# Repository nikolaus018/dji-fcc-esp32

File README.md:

<h1 align="center">dji-fcc-esp32</h1>

<p align="center">
  <b>A pocket dongle that switches a DJI N1 remote to FCC mode, instead of a phone and an app.</b><br>
  Plug it in, it patches over USB, shows the result on an LED and goes back to sleep.
</p>

<p align="center">

</p>

## What is in here

- **Firmware** (ESP-IDF): USB host stack for the remote's CDC-ACM interface, with Espressif's USB component patched to cope with the remote's
  512-byte bulk packets on a full-speed link.
- **Hardware** ([`hardware/`](hardware/README.md)): a complete KiCad design for a battery-powered dongle, generated from one Python source of truth:
  schematic, autorouted 2-layer PCB, gerbers, JLCPCB BOM and placement, STEP model. 0 DRC errors.
- **Web flasher** ([live](https://nikolaus018.github.io/dji-fcc-esp32/), source in [`webflasher/`](webflasher/)): flash either build from Chrome or Edge over Web Serial. Built and deployed by CI on every push.

The two packets come from [DJI-FCC-HACK](https://github.com/M4TH1EU/DJI-FCC-HACK) (credit to galbb on MavicPilots);
this project replaces its Android app.

## Two ways to run it

* **Dev board** (any ESP32-S3 with a native USB port): default build, instructions below.
* **Custom PCB** (battery powered dongle, charge over USB-C, sleeps between uses): see [`hardware/`](hardware/README.md).
  Build the firmware for it with
  ```bash
  idf.py -B build_custom -DSDKCONFIG=sdkconfig.custom -DSDKCONFIG_DEFAULTS=sdkconfig.board_custom -DIDF_TARGET=esp32s3 build
  ```

## Use (dev board)
1. Flash through the **COM** port: `idf.py -p <port> flash`
2. Close the **USB-OTG** solder pad on the board bottom so it can power the remote's port.
3. Power on the drone and remote, wait until connected. The phone must **not** be connected to the remote while patching.
4. Plug the board's **USB** port into the remote's **bottom** port.
5. LED: blue = waiting, yellow = sending, green = sent, red = error.
6. Unplug the board and connect your phone to the **top** port.

The patch must be repeated **every time** you power on the drone and remote.

FCC power is only legal in the US; power cycle the drone and remote to return to CE.

## Flashing the custom PCB
Plug **J2** into your computer and run `idf.py -B build_custom ... -p <port> flash` (port is the ESP's built-in USB-Serial-JTAG). Details in
[`hardware/README.md`](hardware/README.md#flashing-and-updates).

## Notes
- The remote reports 512-byte bulk packets on a full-speed link. `components/espressif__usb` is a copy of
  Espressif's USB host component with the MPS check in `hcd_dwc.c` relaxed, and `main/dji.c` sizes the
  non-periodic TX FIFO for it. Both are required.
- The CDC serial function is interface 2; interfaces 0/1 are DJI-proprietary.
- The LED code drives GPIO48 and GPIO38 (DevKitC-1 v1.0 / v1.1).
- `main/board.h` is the board abstraction (`board_devkit.c` / `board_custom.c`); `main/dji.c` holds the patch logic.
- The dev-board build was tested on a real remote; the custom-PCB firmware compiles but, like the hardware itself, has never run on a real board (see `hardware/README.md`).

## License
MIT for this project's own code (see `LICENSE`). `components/espressif__usb` is Apache-2.0 (Espressif), see its own `LICENSE`.

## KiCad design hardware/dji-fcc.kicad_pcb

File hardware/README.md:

# dji-fcc-esp32 hardware (rev A)

A small battery-powered dongle that replaces the Android phone in the DJI N1 "FCC patch" workflow:
plug it into the remote's **bottom** USB-C port, it powers the port, sends the patch, shows the result on an LED
and goes back to sleep. Charge it over USB-C.

**Status: rev A, ready to order a prototype batch. Not yet built or tested on real hardware.**
Everything below was checked by KiCad ERC/DRC and by cross-checking datasheets; nothing has been powered up.
See [Before you call it production](#before-you-call-it-production).

## What it does

```
 J2 USB-C (charge + flash)     J1 USB-C (to the remote's bottom port)
   │ 5 V, D+/D-                   ▲ 5 V, ~540 mA limit      D+/D-/CC
   ▼                              │                          │
 TP4056 charger ──► VBAT ──► MT3608 boost ──► TPS2553 switch ─┤
 (255 mA)            │  ▲        (5.0 V)        (EN from ESP)  │
                     │  └── DW01A + FS8205A protection        │
                     ▼                                        ▼
                  AP2112K 3.3 V ──► ESP32-S3-MINI-1-N8 ◄─ FSUSB42 ◄─ USBLC6 ESD (J1)
                                      │ ADC: CC1/CC2 (attach), VBAT   ▲   (select = J2 has VBUS)
                                      └ RGB status LED, UART pads     └─ USBLC6 ESD (J2)
```

Behaviour (firmware `main/`, built with `CONFIG_DJI_BOARD_CUSTOM`):

1. Deep sleep (~85 µA). The two CC pins of J1 idle high (33 kΩ pull-ups to 3V3).
2. The remote's 5.1 kΩ Rd pulls a CC pin low on plug-in → ESP wakes (EXT1).
3. Battery check (< 3.3 V → red blinks, sleep). Blue LED. Boost on, switch on → remote gets VBUS and enumerates.
4. Patch is sent over the remote's CDC-ACM interface. Yellow while sending, **green = success, red = failure**.
5. Port power off, deep sleep. Each plug-in is patched once: leaving the dongle in the remote does not keep it
   awake or drain the battery; unplug and plug it in again after every power-on of the drone/remote.

LED colours: blue = powering remote, yellow = sending, green = patched, red = error / low battery.
While J2 is powered the same RGB LED shows charging (red) / full (green) / powered but not charging (blue).

## Files

| Path | What |
|---|---|
| `design.py` | Single source of truth: every part, value, footprint and net. |
| `gen_sch.py` → `dji-fcc.kicad_sch` | Generates the schematic (nets as global labels, one sheet). |
| `gen_pcb.py`, `placement.json`, `route.py`, `tools/route.sh` | Placement → Freerouting → import → ground pours, stitching vias → DRC. |
| `dji-fcc.kicad_pcb` / `.kicad_pro` | The board. Open in KiCad 9/10. |
| `lib/dji_parts.kicad_sym` | Custom symbols (FS8205A, TPS2553). |
| `fab/` | `dji-fcc-gerbers.zip`, `bom_jlcpcb.csv`, `cpl_jlcpcb.csv`, `bom_full.csv`, `dji-fcc.step`, raw gerbers/drill. |
| `docs/` | `schematic.pdf`, `pcb_top.pdf`, `pcb_bottom.pdf`, renders. |

Regenerate everything (needs KiCad, `uv`, Java and Freerouting; paths are set in `tools/env.sh` and can be
overridden with `KICAD_APP`, `JAVA`, `FREEROUTING`):

```bash
cd hardware
uv run --with kiutils python gen_sch.py     # schematic + pin map
PASSES=100 tools/route.sh                   # placement, autoroute (retries), pours, DRC
tools/fab.sh                                # gerbers, drill, BOM, CPL, PDFs, STEP
```

Edit parts/nets in `design.py` and positions in `placement.json`; do not hand-edit the generated KiCad files
unless you stop using the generators.

## Board

* 80 × 34 mm, 1.6 mm, 2-layer, all parts on top (single-sided SMT assembly), 2 mm corner radius.
* Net classes: power 0.6 mm (routed down to 0.4–0.45 mm at pads), signals 0.2 mm, ≥ 0.1 mm minimum, vias 0.6/0.3 (0.8/0.4 power).
* Ground pour on both layers with stitching vias; DRC: 0 errors, 0 unconnected. Schematic parity checked.
* Antenna keepout of the ESP module sits at the top edge (the radio is unused, but nothing is placed there).

### Enclosure interface

| Item | Position (mm, origin top-left, +y down) |
|---|---|
| J1 USB-C (to remote) | mouth flush with left edge, centre y = 17, shell 8.94 wide × 3.3 high |
| J2 USB-C (charge + flash) | mouth flush with right edge, centre y = 17 |
| Status LEDs R/G/B | (67, 2.2), (71, 2.2), (75, 2.2): light-pipe window in the top-right corner |
| Mounting holes | 2 × Ø2.2 (M2) at (3, 31) and (77, 31) |
| Battery | JST-PH 2 mm at (36, 27.4); a 502040 pouch (≈ 5 × 20 × 40 mm, 400-500 mAh) fits under the board |
| Programming/test pads | bottom edge x = 42.5 … 53, y = 32.7 (EN, IO0, TX, RX, 3V3); GND/VBAT/VBUS pads top-left |
| Tallest parts | JST connector 5.5 mm, USB-C 3.3 mm, module 2.4 mm, inductor 2.0 mm |

`fab/dji-fcc.step` contains the board and component models for fitting a case. Keep metal away from the top edge
(antenna end of the module). Both USB-C ports are exposed in the default layout. J2 is needed for charging and updates, so a case that hides it needs a cover or
a charge/update door; J1 is the one used every flight.

## Ordering (JLCPCB)

1. Upload `fab/dji-fcc-gerbers.zip`: 2 layers, 1.6 mm, any surface finish (HASL is fine; ENIG nicer for USB-C).
2. Enable SMT assembly, **top side**, upload `fab/bom_jlcpcb.csv` and `fab/cpl_jlcpcb.csv`.
3. In the placement viewer **check rotation of every polarised part** (U1..U7, Q1, J1..J3, D1..D8, L1).
   JLCPCB's part library often needs per-part rotation offsets (`cpl_jlcpcb.csv` uses KiCad's rotation as-is).
4. Hand-fit afterwards: battery (pre-wired JST-PH 2.0 pack, **polarity: + on pin 1, silkscreen shows + and -**).
   Many packs are wired the other way round; check with a meter before connecting.
5. Flash over J2 (below), then run the bring-up list.

`fab/bom_full.csv` lists every line with MPN and LCSC number. Numbers were looked up on jlcpcb.com on 2026-10-11:
every line resolved to a matching part (L1, C48427, is listed as Sunlord SWPA4020S4R7MT, 4.7 µH, rated 1.34 A / 2.5 A). **Stock and "basic vs extended" status change, re-check before ordering.**
Q1 is ordered as HXY MOSFET 8205A (C5148694) because the Fortune FS8205A was out of stock; 8205A parts in TSSOP-8
share one pinout (1/8 drain, 2/3 source 1, 4 gate 1, 5 gate 2, 6/7 source 2), and the HXY datasheet drawing matches it.
The DW01A pin order was checked against the YONGYUTAI datasheet for C2927799 (1 OD, 2 CSI, 3 OC, 4 NC, 5 VDD,
6 VSS; over-charge 4.30 V, over-discharge 2.40 V).

## Flashing and updates

**Over J2 (USB-C), no adapter needed.** The ESP32-S3 has one USB port. A small switch (FSUSB42) connects it to J2 whenever J2 has
5 V on it (a computer or charger plugged in) and to J1 otherwise. Plug J2 into a computer:

1. The board wakes (VBUS on J2 is a wake source), sees the charger and stays out of USB host mode. The RGB LED shows charge state.
2. The ESP's built-in USB-Serial-JTAG shows up as a serial port (VID 303A, PID 1001).
3. `idf.py -B build_custom ... -p <port> flash`. esptool resets into the ROM bootloader by itself (no buttons).

If the firmware is ever broken so badly that step 2 does not work, short the **IO0** pad to GND while plugging J2 in: the ROM
bootloader takes over USB. The UART pads (TX, RX, GND, 3V3, EN, IO0) remain as a last resort and for production jigs.
Do not power the 3V3 pad while the battery is connected.

On a computer the ESP stays awake for as long as the host talks to it, so the port does not disappear mid-flash.
On a plain charger it sleeps and only wakes every 30 s for about 2 s to refresh the LED (which stays lit through
the sleep). That matters: the awake ESP draws more than the TP4056's 25 mA end-of-charge threshold, so a board that
stayed awake would never finish charging. For the same reason the LED may not reach green while J2 is on a computer.

## Design notes

* **Remote port:** Rp = 33 kΩ to 3V3 on both CC pins (spec: 36 kΩ ±20 % = default USB power). VBUS comes from an
  MT3608 boost (FB divider 220 k/30 k → 5.0 V) through a TPS2553 (R_ILIM 47 kΩ ≈ 540 mA, reverse-blocking, /FAULT to the ESP).
  The boost output is not isolated when disabled (battery minus a diode drop leaks to its output), the switch is what keeps the port dead.
* **Charger:** TP4056, R_PROG 4.7 kΩ → 255 mA (≈ 0.5 C for a 500 mAh cell), TEMP tied to GND (no NTC), CE tied high.
* **Protection:** DW01A + FS8205A in the battery negative leg (net `BNEG` ↔ `GND`), so the pack cannot over-discharge even
  if the firmware misbehaves. Still use a good cell; protection ICs are not a substitute.
* **LDO:** AP2112K-3.3 directly from VBAT. Below ≈ 3.55 V the rail sags (dropout), the firmware refuses to start the remote below 3.3 V.
* **Sleep current:** AP2112K 55 µA + S3 deep sleep ~7 µA + DW01A ~3 µA + dividers ~17 µA ≈ 85 µA → months of standby on 500 mAh.
* **Status LEDs** sit between VBAT and the GPIOs (sinking, GPIO low = on) so the blue LED still has headroom at 3.3 V.
* **USB data path:** FSUSB42 (VCC 3.3 V, OE tied low, SEL = J2-VBUS divider output). SEL low → J1 (remote), SEL high → J2 (computer).
  Each connector has its own USBLC6 ESD array.
* **Pins used:** IO1/IO2 CC1/CC2 (ADC1, wake), IO4 VBAT sense (ADC1), IO6 boost EN, IO7 switch EN, IO8 /FAULT, IO21 J2-VBUS sense (wake),
  IO38 /STDBY, IO39 /CHRG (internal pull-ups), IO40/41/42 LED B/G/R, IO19/IO20 USB, TXD0/RXD0 UART pads, IO0/EN pads.

## Before you call it production

This is a prototype-ready design, not a production release. Open items, roughly in order:

1. **Build 5 boards and bring them up.** Checklist:
   - Visual / continuity: no shorts VBAT-GND, 3V3-GND, VBUS_REM-GND with the battery out.
   - Charge port: 5 V in → RGB LED red while charging, green when full, TP4056 BAT ≈ 4.2 V at end of charge, 255 mA max.
   - **USB switch:** with J2 on a computer the ESP enumerates as 303A:1001 and flashes; with only J1 plugged into a remote it enumerates the remote.
     Check both directions, also with both cables attached (J2 wins).
   - Protection: a DW01A usually stays off after the battery is first connected until a charger is applied once;
     plug J2 in before judging a "dead" board. Then, battery connected, measure VBAT at J3 vs. 3V3 pad; short-circuit test on a bench supply with current limit.
   - Boost: VBOOST = 5.0 V ± 3 % with 100 Ω load, ripple < 100 mV; `BOOST_EN` low → switch output < 0.1 V.
   - Switch: VBUS_REM = 0 V when idle, 5 V when enabled, trips at ≈ 0.5-0.6 A.
   - **J1 CC behaviour with a real remote:** confirm CC reads ≈ 0.44 V when plugged and the board wakes. If a remote variant
     does not present Rd, the wake logic needs a fallback (timer wake + VBUS probe). Also check that unplugging wakes
     the board once and that it then sleeps again (the firmware re-arms the wake-up for the opposite CC level).
   - Sleep / charge: sleep current ≈ 85 µA with and without a remote left plugged in; on a wall charger the LED goes
     red → green and the TP4056 terminates.
   - Full patch cycle on every drone/remote you care about (README of DJI-FCC-HACK lists tested ones).
2. **Verify placement rotations** in the JLCPCB viewer and on the first assembled board.
3. **Battery:** a protected 1S LiPo with PH-2.0 lead and the polarity you expect. Mechanical retention and a label on the case.
4. **Compliance** (needed to sell it): FCC Part 15B / CE EMC for an unintentional radiator that contains a pre-certified module,
   UN38.3 transport test for the battery, RoHS paperwork. Also check the legal side of selling a product whose purpose is to switch
   a DJI remote to its FCC power profile.
5. Firmware: measure the brown-out margin with a nearly empty cell (a brown-out reset is reported as low battery and
   not retried until the next plug-in).

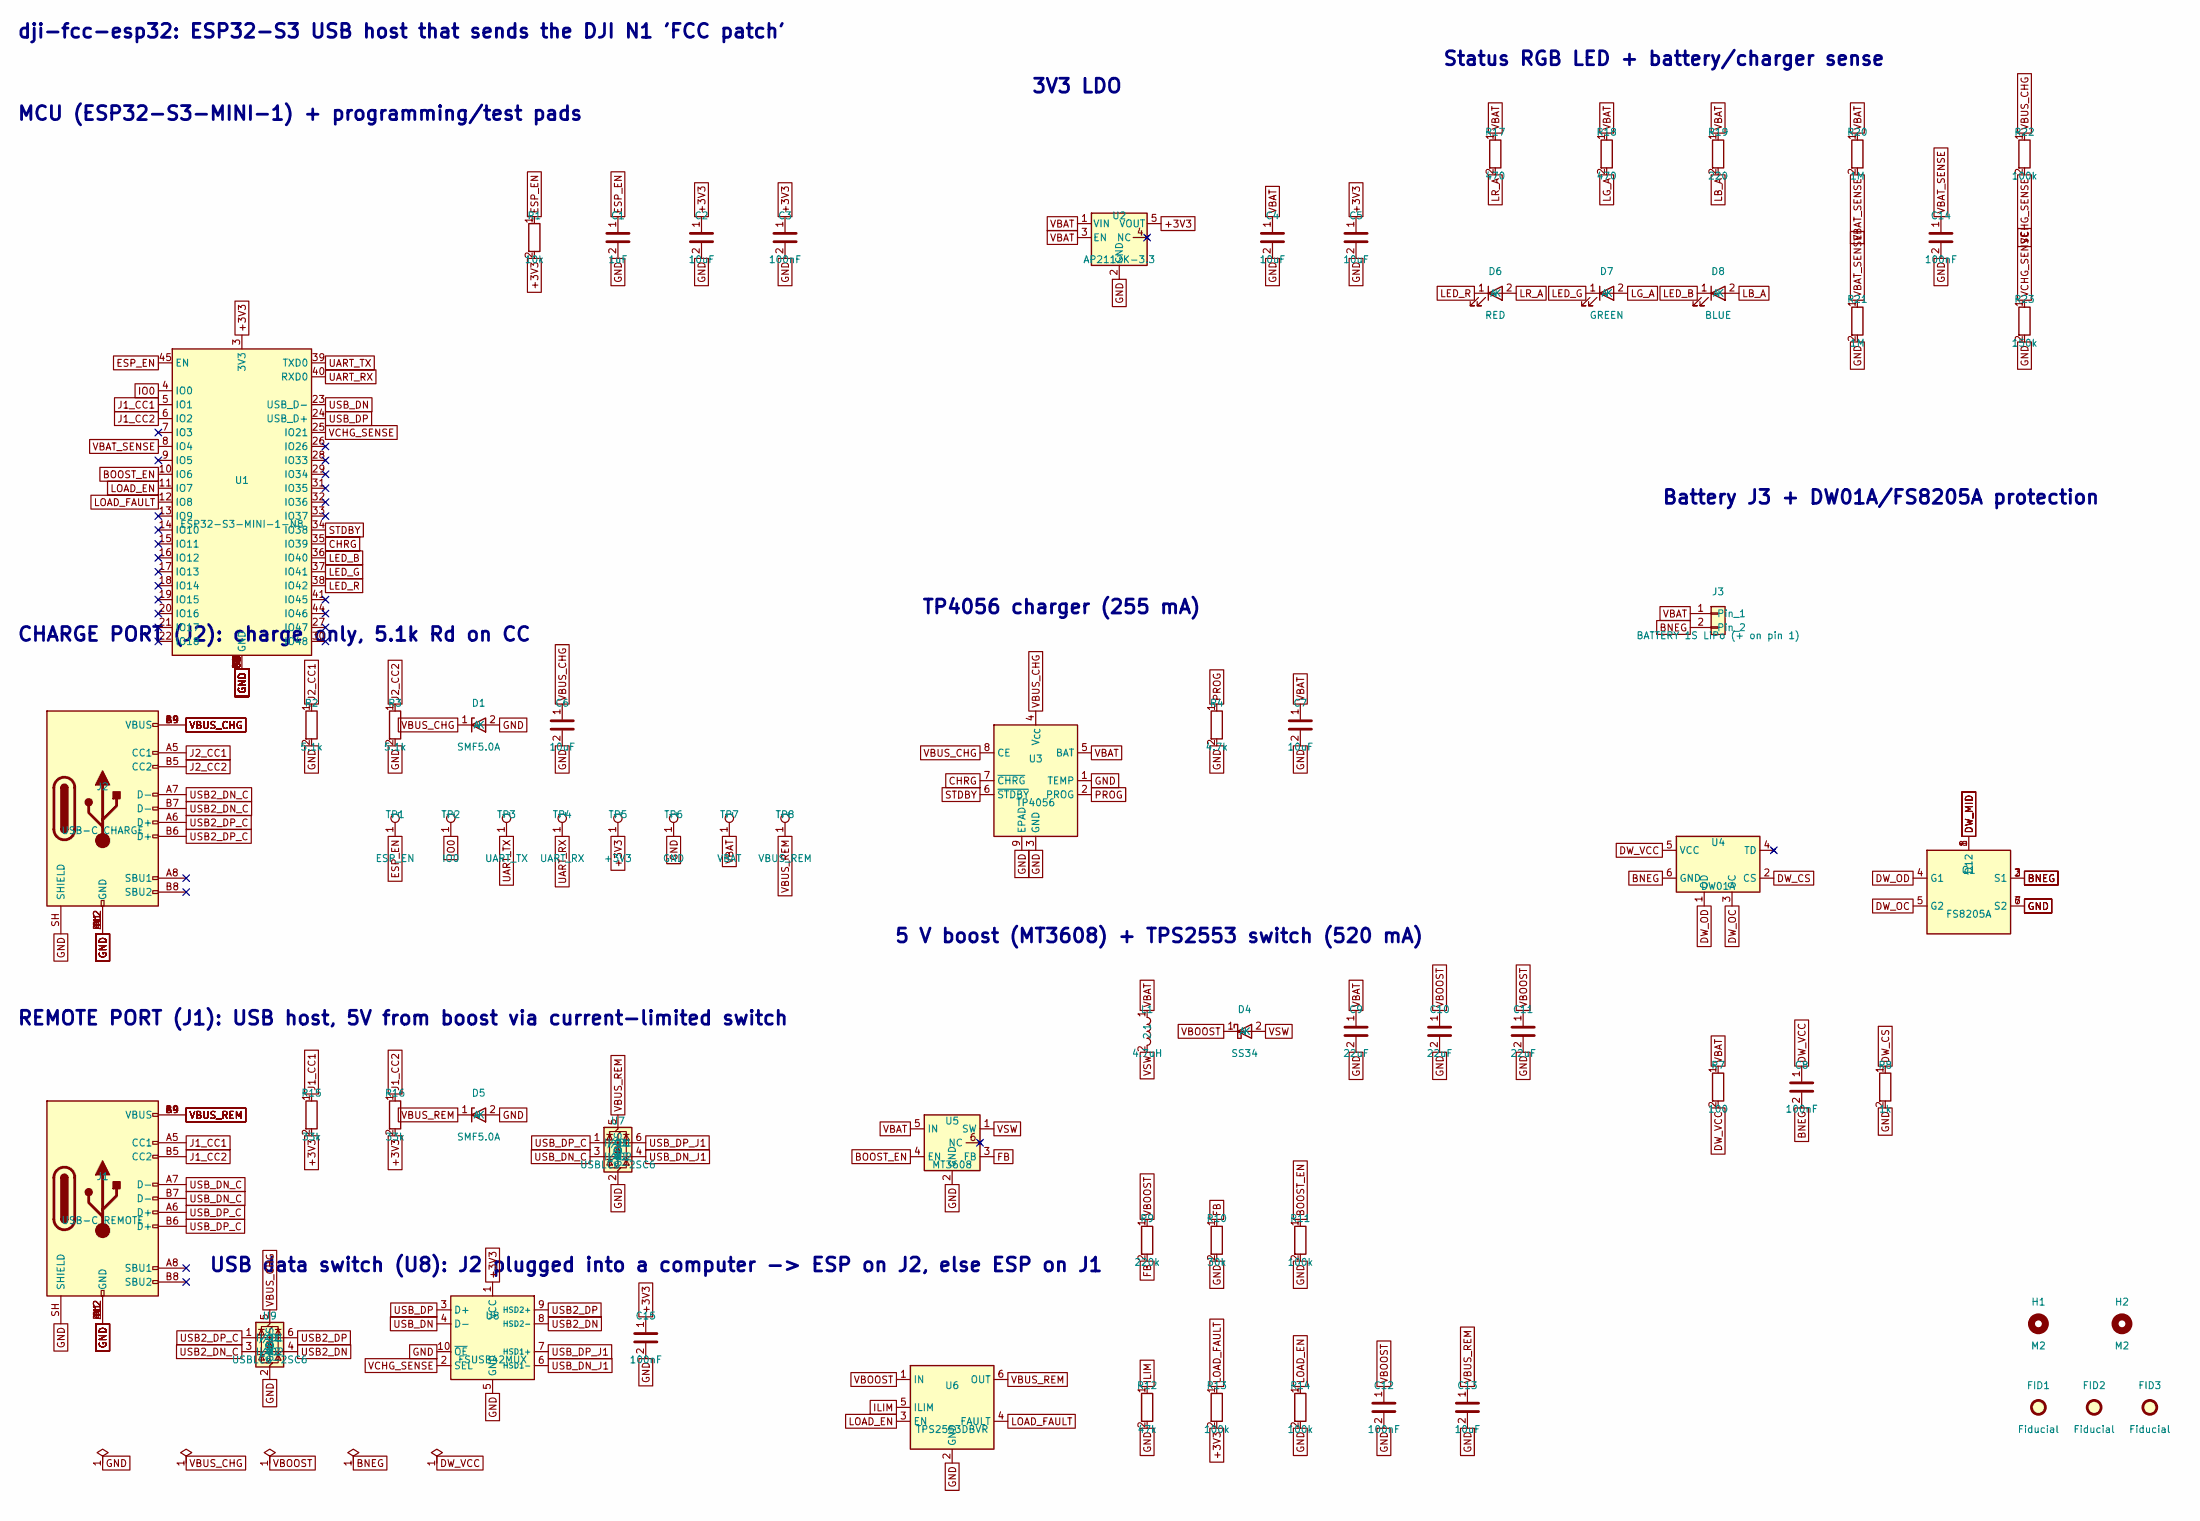
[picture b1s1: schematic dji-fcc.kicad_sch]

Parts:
C1: 1uF; C_0603_1608Metric
C2, C4, C5, C6, C7, C13: 10uF; C_0805_2012Metric
C3, C8, C12, C14, C15: 100nF; C_0603_1608Metric
C9, C10, C11: 22uF; C_0805_2012Metric
D1, D5: SMF5.0A; D_SOD-123F; MPN SMF5.0A
D4: SS34; D_SMA; MPN SS34
D6: RED; LED_0603_1608Metric
D7: GREEN; LED_0603_1608Metric
D8: BLUE; LED_0603_1608Metric
FID1, FID2, FID3: Fiducial; Fiducial_0.5mm_Mask1mm
H1, H2: M2; MountingHole_2.2mm_M2
J1: USB-C REMOTE; USB_C_Receptacle_HRO_TYPE-C-31-M-12; MPN TYPE-C-31-M-12
J2: USB-C CHARGE; USB_C_Receptacle_HRO_TYPE-C-31-M-12; MPN TYPE-C-31-M-12
J3: BATTERY 1S LiPo (+ on pin 1); JST_PH_S2B-PH-SM4-TB_1x02-1MP_P2.00mm_Horizontal; MPN S2B-PH-SM4-TB
L1: 4.7uH; L_Sunlord_SWPA4020S; MPN SWPA4020S4R7MT
Q1: FS8205A; TSSOP-8_4.4x3mm_P0.65mm; MPN FS8205A
R1: 10k; R_0603_1608Metric
R2, R3: 5.1k; R_0603_1608Metric
R4: 4.7k; R_0603_1608Metric
R7: 100; R_0603_1608Metric
R8: 1k; R_0603_1608Metric
R9: 220k; R_0603_1608Metric
R10: 30k; R_0603_1608Metric
R11, R13, R14, R22: 100k; R_0603_1608Metric
R12: 47k; R_0603_1608Metric
R15, R16: 33k; R_0603_1608Metric
R17, R18: 470; R_0603_1608Metric
R19: 220; R_0603_1608Metric
R20, R21: 1M; R_0603_1608Metric
R23: 150k; R_0603_1608Metric
TP1: ESP_EN; TestPoint_Pad_D1.5mm
TP2: IO0; TestPoint_Pad_D1.5mm
TP3: UART_TX; TestPoint_Pad_D1.5mm
TP4: UART_RX; TestPoint_Pad_D1.5mm
TP5: +3V3; TestPoint_Pad_D1.5mm
TP6: GND; TestPoint_Pad_D1.5mm
TP7: VBAT; TestPoint_Pad_D1.5mm
TP8: VBUS_REM; TestPoint_Pad_D1.5mm
U1: ESP32-S3-MINI-1-N8; ESP32-S2-MINI-1; MPN ESP32-S3-MINI-1-N8
U2: AP2112K-3.3; SOT-23-5; MPN AP2112K-3.3TRG1
U3: TP4056; SOIC-8-1EP_3.9x4.9mm_P1.27mm_EP2.41x3.3mm; MPN TP4056-42-ESOP8
U4: DW01A; SOT-23-6; MPN DW01A
U5: MT3608; SOT-23-6; MPN MT3608
U6: TPS2553DBVR; SOT-23-6; MPN TPS2553DBVR
U7, U9: USBLC6-2SC6; SOT-23-6; MPN USBLC6-2SC6
U8: FSUSB42MUX; MSOP-10_3x3mm_P0.5mm; MPN FSUSB42MUX

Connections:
+3V3: C2.1, C3.1, C5.1, C15.1, R1.2, R13.2, R15.2, R16.2, TP5.1, U1.3 (3V3), U2.5 (VOUT), U8.1 (VCC)
BNEG: C8.2, J3.2, Q1.2 (S1), Q1.3 (S1), U4.6 (GND)
BOOST_EN: R11.1, U1.10 (IO6), U5.4 (EN)
CHRG: U1.35 (IO39), U3.7 (~CHRG)
DW_CS: R8.1, U4.2 (CS)
DW_MID: Q1.1 (D12), Q1.8 (D12)
DW_OC: Q1.5 (G2), U4.3 (OC)
DW_OD: Q1.4 (G1), U4.1 (OD)
DW_VCC: C8.1, R7.2, U4.5 (VCC)
ESP_EN: C1.1, R1.1, TP1.1, U1.45 (EN)
FB: R9.2, R10.1, U5.3 (FB)
GND: C1.2, C2.2, C3.2, C4.2, C5.2, C6.2, C7.2, C9.2, C10.2, C11.2, C12.2, C13.2, C14.2, C15.2, D1.2 (A), D5.2 (A), J1.A1 (GND), J1.A12 (GND), J1.B1 (GND), J1.B12 (GND), J1.SH (SHIELD), J2.A1 (GND), J2.A12 (GND), J2.B1 (GND), J2.B12 (GND), J2.SH (SHIELD), Q1.6 (S2), Q1.7 (S2), R2.2, R3.2, R4.2, R8.2, R10.2, R11.2, R12.2, R14.2, R21.2, R23.2, TP6.1, U1.1 (GND), U1.2 (GND), U1.42 (GND), U1.43 (GND), U1.46 (GND), U1.47 (GND), U1.48 (GND), U1.49 (GND), U1.50 (GND), U1.51 (GND), U1.52 (GND), U1.53 (GND), U1.54 (GND), U1.55 (GND), U1.56 (GND), U1.57 (GND), U1.58 (GND), U1.59 (GND), U1.60 (GND), U1.61 (GND), U1.62 (GND), U1.63 (GND), U1.64 (GND), U1.65 (GND), U2.2 (GND), U3.1 (TEMP), U3.3 (GND), U3.9 (EPAD), U5.2 (GND), U6.2 (GND), U7.2 (GND), U8.5 (GND), U8.10 (~OE), U9.2 (GND)
ILIM: R12.1, U6.5 (ILIM)
IO0: TP2.1, U1.4 (IO0)
J1_CC1: J1.A5 (CC1), R15.1, U1.5 (IO1)
J1_CC2: J1.B5 (CC2), R16.1, U1.6 (IO2)
J2_CC1: J2.A5 (CC1), R2.1
J2_CC2: J2.B5 (CC2), R3.1
LB_A: D8.2 (A), R19.2
LED_B: D8.1 (K), U1.36 (IO40)
LED_G: D7.1 (K), U1.37 (IO41)
LED_R: D6.1 (K), U1.38 (IO42)
LG_A: D7.2 (A), R18.2
LOAD_EN: R14.1, U1.11 (IO7), U6.3 (EN)
LOAD_FAULT: R13.1, U1.12 (IO8), U6.4 (FAULT)
LR_A: D6.2 (A), R17.2
PROG: R4.1, U3.2 (PROG)
STDBY: U1.34 (IO38), U3.6 (~STDBY)
UART_RX: TP4.1, U1.40 (RXD0)
UART_TX: TP3.1, U1.39 (TXD0)
USB2_DN: U8.8 (HSD2-), U9.4 (I/O2)
USB2_DN_C: J2.A7 (D-), J2.B7 (D-), U9.3 (I/O2)
USB2_DP: U8.9 (HSD2+), U9.6 (I/O1)
USB2_DP_C: J2.A6 (D+), J2.B6 (D+), U9.1 (I/O1)
USB_DN: U1.23 (USB_D-), U8.4 (D-)
USB_DN_C: J1.A7 (D-), J1.B7 (D-), U7.3 (I/O2)
USB_DN_J1: U7.4 (I/O2), U8.6 (HSD1-)
USB_DP: U1.24 (USB_D+), U8.3 (D+)
USB_DP_C: J1.A6 (D+), J1.B6 (D+), U7.1 (I/O1)
USB_DP_J1: U7.6 (I/O1), U8.7 (HSD1+)
VBAT: C4.1, C7.1, C9.1, J3.1, L1.1, R7.1, R17.1, R18.1, R19.1, R20.1, TP7.1, U2.1 (VIN), U2.3 (EN), U3.5 (BAT), U5.5 (IN)
VBAT_SENSE: C14.1, R20.2, R21.1, U1.8 (IO4)
VBOOST: C10.1, C11.1, C12.1, D4.1 (K), R9.1, U6.1 (IN)
VBUS_CHG: C6.1, D1.1 (K), J2.A4 (VBUS), J2.A9 (VBUS), J2.B4 (VBUS), J2.B9 (VBUS), R22.1, U3.4 (V_{CC}), U3.8 (CE), U9.5 (VBUS)
VBUS_REM: C13.1, D5.1 (K), J1.A4 (VBUS), J1.A9 (VBUS), J1.B4 (VBUS), J1.B9 (VBUS), TP8.1, U6.6 (OUT), U7.5 (VBUS)
VCHG_SENSE: R22.2, R23.1, U1.25 (IO21), U8.2 (SEL)
VSW: D4.2 (A), L1.2, U5.1 (SW)

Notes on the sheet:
dji-fcc-esp32: ESP32-S3 USB host that sends the DJI N1 'FCC patch'
MCU (ESP32-S3-MINI-1) + programming/test pads
3V3 LDO
Status RGB LED + battery/charger sense
REMOTE PORT (J1): USB host, 5V from boost via current-limited switch
5 V boost (MT3608) + TPS2553 switch (520 mA)
USB data switch (U8): J2 plugged into a computer -> ESP on J2, else ESP on J1
CHARGE PORT (J2): charge only, 5.1k Rd on CC
TP4056 charger (255 mA)
Battery J3 + DW01A/FS8205A protection

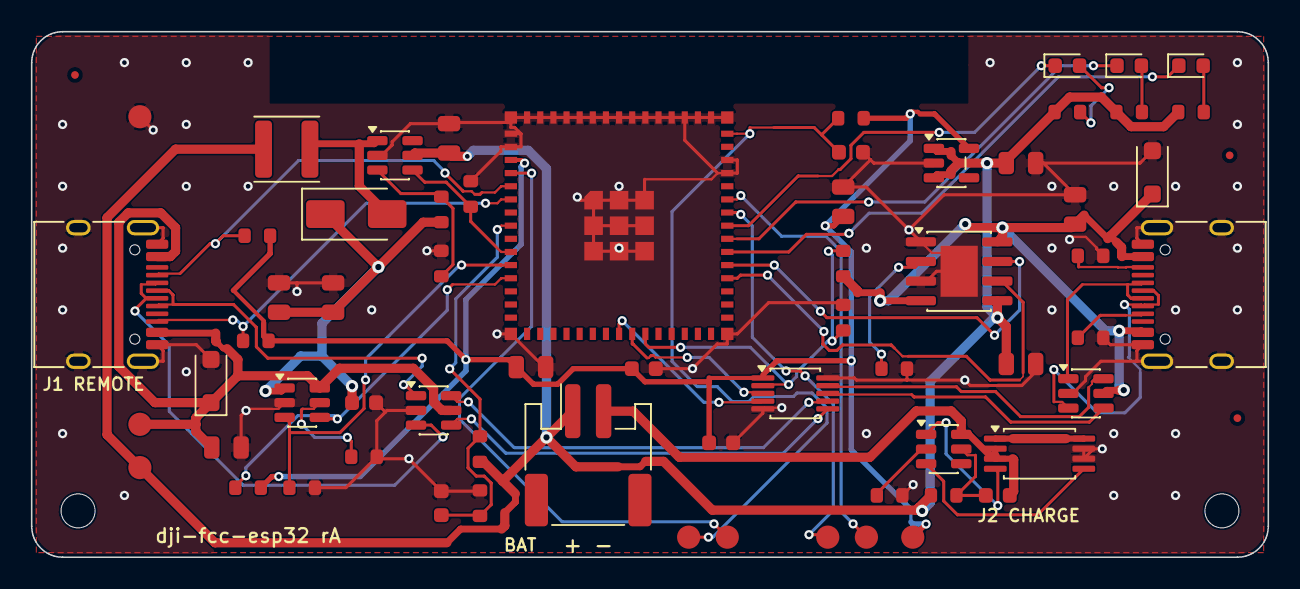
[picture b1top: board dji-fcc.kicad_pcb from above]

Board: 2 copper layers, 80.0 x 34.0 mm, 69 parts (0 on the bottom side), 47 nets.

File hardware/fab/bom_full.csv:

Qty,Value,Designators,Footprint,MPN,LCSC,Missing LCSC?
1,1uF,C1,C_0603_1608Metric,,C15849,
6,10uF,C2 C4 C5 C6 C7 C13,C_0805_2012Metric,,C15850,
5,100nF,C3 C8 C12 C14 C15,C_0603_1608Metric,,C14663,
3,22uF,C9 C10 C11,C_0805_2012Metric,,C45783,
2,SMF5.0A,D1 D5,D_SOD-123F,SMF5.0A,C707993,
1,SS34,D4,D_SMA,SS34,C8678,
1,RED,D6,LED_0603_1608Metric,,C2286,
1,GREEN,D7,LED_0603_1608Metric,,C72043,
1,BLUE,D8,LED_0603_1608Metric,,C72041,
1,USB-C REMOTE,J1,USB_C_Receptacle_HRO_TYPE-C-31-M-12,TYPE-C-31-M-12,C165948,
1,USB-C CHARGE,J2,USB_C_Receptacle_HRO_TYPE-C-31-M-12,TYPE-C-31-M-12,C165948,
1,BATTERY 1S LiPo (+ on pin 1),J3,JST_PH_S2B-PH-SM4-TB_1x02-1MP_P2.00mm_Horizontal,S2B-PH-SM4-TB,C295747,
1,4.7uH,L1,L_Sunlord_SWPA4020S,SWPA4020S4R7MT,C48427,
1,FS8205A,Q1,TSSOP-8_4.4x3mm_P0.65mm,FS8205A,C14212,
1,10k,R1,R_0603_1608Metric,,C25804,
2,5.1k,R2 R3,R_0603_1608Metric,,C23186,
1,4.7k,R4,R_0603_1608Metric,,C23162,
1,100,R7,R_0603_1608Metric,,C22775,
1,1k,R8,R_0603_1608Metric,,C21190,
1,220k,R9,R_0603_1608Metric,,C22961,
1,30k,R10,R_0603_1608Metric,,C22984,
4,100k,R11 R13 R14 R22,R_0603_1608Metric,,C25803,
1,47k,R12,R_0603_1608Metric,,C25819,
2,33k,R15 R16,R_0603_1608Metric,,C4216,
2,470,R17 R18,R_0603_1608Metric,,C23179,
1,220,R19,R_0603_1608Metric,,C22962,
2,1M,R20 R21,R_0603_1608Metric,,C22935,
1,150k,R23,R_0603_1608Metric,,C22807,
1,ESP32-S3-MINI-1-N8,U1,ESP32-S2-MINI-1,ESP32-S3-MINI-1-N8,C2913206,
1,AP2112K-3.3,U2,SOT-23-5,AP2112K-3.3TRG1,C51118,
1,TP4056,U3,SOIC-8-1EP_3.9x4.9mm_P1.27mm_EP2.41x3.3mm,TP4056-42-ESOP8,C16581,
1,DW01A,U4,SOT-23-6,DW01A,C2927799,
1,MT3608,U5,SOT-23-6,MT3608,C84817,
1,TPS2553DBVR,U6,SOT-23-6,TPS2553DBVR,C55266,
2,USBLC6-2SC6,U7 U9,SOT-23-6,USBLC6-2SC6,C7519,
1,FSUSB42MUX,U8,MSOP-10_3x3mm_P0.5mm,FSUSB42MUX,C11355,

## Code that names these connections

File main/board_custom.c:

#include "sdkconfig.h"
#if CONFIG_DJI_BOARD_CUSTOM
#include "board.h"
#include "driver/gpio.h"
#include "driver/usb_serial_jtag.h"
#include "esp_adc/adc_cali.h"
#include "esp_adc/adc_cali_scheme.h"
#include "esp_adc/adc_oneshot.h"
#include "esp_log.h"
#include "esp_sleep.h"
#include "freertos/FreeRTOS.h"
#include "freertos/task.h"

// GPIO map of hardware/design.py (net -> pin)
#define PIN_CC1        1    // J1_CC1, ADC1_CH0, 33k pull-up to 3V3, remote pulls down with 5.1k
#define PIN_CC2        2    // J1_CC2, ADC1_CH1
#define PIN_VBAT_SENSE 4    // ADC1_CH3, 1M/1M divider from VBAT
#define PIN_BOOST_EN   6    // MT3608 EN
#define PIN_LOAD_EN    7    // TPS2553 EN
#define PIN_LOAD_FAULT 8    // TPS2553 /FAULT, external 100k pull-up
#define PIN_VCHG_SENSE 21   // J2 VBUS via 100k/150k divider (RTC GPIO); also the USB switch select
#define PIN_CHRG       39   // TP4056 /CHRG  (open drain, low = charging)
#define PIN_STDBY      38   // TP4056 /STDBY (open drain, low = done)
#define PIN_LED_R      42   // LED cathodes: anodes sit on VBAT, GPIO low = on
#define PIN_LED_G      41
#define PIN_LED_B      40

#define ADC_CH_CC1  ADC_CHANNEL_0
#define ADC_CH_CC2  ADC_CHANNEL_1
#define ADC_CH_VBAT ADC_CHANNEL_3
// Rp 33k to 3V3: an open CC pin reads >3 V, the remote's Rd (5.1k) ~0.44 V, the Ra (<=1.2k) of an
// electronically marked cable <0.12 V. Only Rd counts as "remote attached".
#define CC_OPEN_MV 1600
#define CC_RA_MV   220

static const char *TAG = "board";
static adc_oneshot_unit_handle_t adc;
static adc_cali_handle_t cali;

static int adc_mv(adc_channel_t ch)
{
    int sum = 0, raw = 0;
    for (int i = 0; i < 8; i++) {
        adc_oneshot_read(adc, ch, &raw);
        sum += raw;
    }
    int mv = 0;
    adc_cali_raw_to_voltage(cali, sum / 8, &mv);
    return mv;
}

// Sorts the two CC pins into "sees Rd" and "open" GPIO masks (a pin on Ra is in neither).
static void cc_read(uint64_t *rd, uint64_t *open)
{
    static const struct { adc_channel_t ch; int pin; } CC[] = {{ADC_CH_CC1, PIN_CC1}, {ADC_CH_CC2, PIN_CC2}};
    *rd = *open = 0;
    for (int i = 0; i < 2; i++) {
        int mv = adc_mv(CC[i].ch);
        if (mv >= CC_OPEN_MV) {
            *open |= BIT64(CC[i].pin);
        } else if (mv > CC_RA_MV) {
            *rd |= BIT64(CC[i].pin);
        }
    }
}

static bool cc_attached(void)
{
    uint64_t rd, open;
    cc_read(&rd, &open);
    return rd != 0;
}

void board_init(void)
{
    const gpio_config_t outs = {
        .pin_bit_mask = BIT64(PIN_BOOST_EN) | BIT64(PIN_LOAD_EN) | BIT64(PIN_LED_R) | BIT64(PIN_LED_G) | BIT64(PIN_LED_B),
        .mode = GPIO_MODE_OUTPUT,
    };
    gpio_config(&outs);
    gpio_set_level(PIN_BOOST_EN, 0);
    gpio_set_level(PIN_LOAD_EN, 0);
    board_led(0, 0, 0);
    // board_charge_sleep() keeps the LED pins latched through deep sleep; release them again
    gpio_deep_sleep_hold_dis();
    gpio_hold_dis(PIN_LED_R);
    gpio_hold_dis(PIN_LED_G);
    gpio_hold_dis(PIN_LED_B);
    gpio_config(&(gpio_config_t){.pin_bit_mask = BIT64(PIN_LOAD_FAULT) | BIT64(PIN_VCHG_SENSE), .mode = GPIO_MODE_INPUT});
    gpio_config(&(gpio_config_t){.pin_bit_mask = BIT64(PIN_CHRG) | BIT64(PIN_STDBY), .mode = GPIO_MODE_INPUT,
                                 .pull_up_en = GPIO_PULLUP_ENABLE});

    adc_oneshot_unit_init_cfg_t unit = {.unit_id = ADC_UNIT_1};
    ESP_ERROR_CHECK(adc_oneshot_new_unit(&unit, &adc));
    adc_oneshot_chan_cfg_t ch = {.atten = ADC_ATTEN_DB_12, .bitwidth = ADC_BITWIDTH_DEFAULT};
    ESP_ERROR_CHECK(adc_oneshot_config_channel(adc, ADC_CH_CC1, &ch));
    ESP_ERROR_CHECK(adc_oneshot_config_channel(adc, ADC_CH_CC2, &ch));
    ESP_ERROR_CHECK(adc_oneshot_config_channel(adc, ADC_CH_VBAT, &ch));
    adc_cali_curve_fitting_config_t cc = {.unit_id = ADC_UNIT_1, .atten = ADC_ATTEN_DB_12, .bitwidth = ADC_BITWIDTH_DEFAULT};
    ESP_ERROR_CHECK(adc_cali_create_scheme_curve_fitting(&cc, &cali));
}

void board_led(uint8_t r, uint8_t g, uint8_t b)
{
    gpio_set_level(PIN_LED_R, !r);
    gpio_set_level(PIN_LED_G, !g);
    gpio_set_level(PIN_LED_B, !b);
}

int board_battery_mv(void)
{
    return adc_mv(ADC_CH_VBAT) * 2;   // 1M/1M divider
}

bool board_wait_remote_attach(int timeout_ms)
{
    int stable = 0;
    for (int t = 0; t <= timeout_ms; t += 50) {
        stable = cc_attached() ? stable + 1 : 0;
        if (stable >= 3) {
            return true;
        }
        vTaskDelay(pdMS_TO_TICKS(50));
    }
    return false;
}

void board_remote_power(bool on)
{
    if (on) {
        gpio_set_level(PIN_BOOST_EN, 1);
        vTaskDelay(pdMS_TO_TICKS(20));      // let the 5 V rail come up before closing the switch
        gpio_set_level(PIN_LOAD_EN, 1);
    } else {
        gpio_set_level(PIN_LOAD_EN, 0);
        gpio_set_level(PIN_BOOST_EN, 0);
    }
}

bool board_remote_fault(void)
{
    return gpio_get_level(PIN_LOAD_FAULT) == 0;
}

bool board_charger_present(void)
{
    return gpio_get_level(PIN_VCHG_SENSE) == 1;
}

int board_charge_state(void)
{
    if (gpio_get_level(PIN_CHRG) == 0) {
        return 1;
    }
    return gpio_get_level(PIN_STDBY) == 0 ? 2 : 0;
}

bool board_usb_host_connected(void)
{
    return usb_serial_jtag_is_connected();
}

void board_sleep(void)
{
    board_remote_power(false);
    board_led(0, 0, 0);
    // Both CC pins idle high (33k pull-up); the remote's 5.1k Rd pulls one of them low. EXT1 is level
    // triggered, so arm it for the next change: unplug while a remote is attached, plug-in otherwise.
    uint64_t rd, open;
    cc_read(&rd, &open);
    if (rd) {
        ESP_LOGI(TAG, "deep sleep, waking when the remote is unplugged");
        esp_sleep_enable_ext1_wakeup_io(rd, ESP_EXT1_WAKEUP_ANY_HIGH);
    } else if (open) {
        ESP_LOGI(TAG, "deep sleep, waking when a remote is plugged in");
        esp_sleep_enable_ext1_wakeup_io(open, ESP_EXT1_WAKEUP_ANY_LOW);
    }
    // Plugging J2 into a charger/computer also wakes us (VBUS high) so USB flashing works from sleep.
    esp_sleep_enable_ext0_wakeup(PIN_VCHG_SENSE, 1);
    esp_deep_sleep_start();
}

void board_charge_sleep(int seconds)
{
    board_remote_power(false);
    gpio_hold_en(PIN_LED_R);
    gpio_hold_en(PIN_LED_G);
    gpio_hold_en(PIN_LED_B);
    gpio_deep_sleep_hold_en();
    esp_sleep_enable_timer_wakeup(seconds * 1000000ULL);
    esp_sleep_enable_ext0_wakeup(PIN_VCHG_SENSE, 0);   // J2 unplugged
    esp_deep_sleep_start();
}
#endif

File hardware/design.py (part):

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R("R4", "4.7k", "PROG", "GND")  # 1200/4.7k = ~255 mA charge current
C("C7", "10uF", "VBAT", "GND", fp=C0805)
part("J3", "Connector_Generic:Conn_01x02", "Connector_JST:JST_PH_S2B-PH-SM4-TB_1x02-1MP_P2.00mm_Horizontal",
     "BATTERY 1S LiPo (+ on pin 1)", {"1": "VBAT", "2": "BNEG"}, mpn="S2B-PH-SM4-TB")
part("U4", "Battery_Management:DW01A", SOT236, "DW01A",
     {"OD": "DW_OD", "CS": "DW_CS", "OC": "DW_OC", "VCC": "DW_VCC", "GND": "BNEG"}, mpn="DW01A")
part("Q1", "dji_parts:FS8205A", "Package_SO:TSSOP-8_4.4x3mm_P0.65mm", "FS8205A",
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part("U5", "Regulator_Switching:MT3608", SOT236, "MT3608",
     {"SW": "VSW", "GND": "GND", "FB": "FB", "EN": "BOOST_EN", "IN": "VBAT"}, mpn="MT3608")
passive("L1", "Device:L", "Inductor_SMD:L_Sunlord_SWPA4020S", "4.7uH", "VBAT", "VSW", mpn="SWPA4020S4R7MT")
passive("D4", "Device:D_Schottky", "Diode_SMD:D_SMA", "SS34", "VBOOST", "VSW", mpn="SS34")  # K=1, A=2
C("C9", "22uF", "VBAT", "GND", fp=C0805)
C("C10", "22uF", "VBOOST", "GND", fp=C0805)
C("C11", "22uF", "VBOOST", "GND", fp=C0805)
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

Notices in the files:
README.md:
MIT license
